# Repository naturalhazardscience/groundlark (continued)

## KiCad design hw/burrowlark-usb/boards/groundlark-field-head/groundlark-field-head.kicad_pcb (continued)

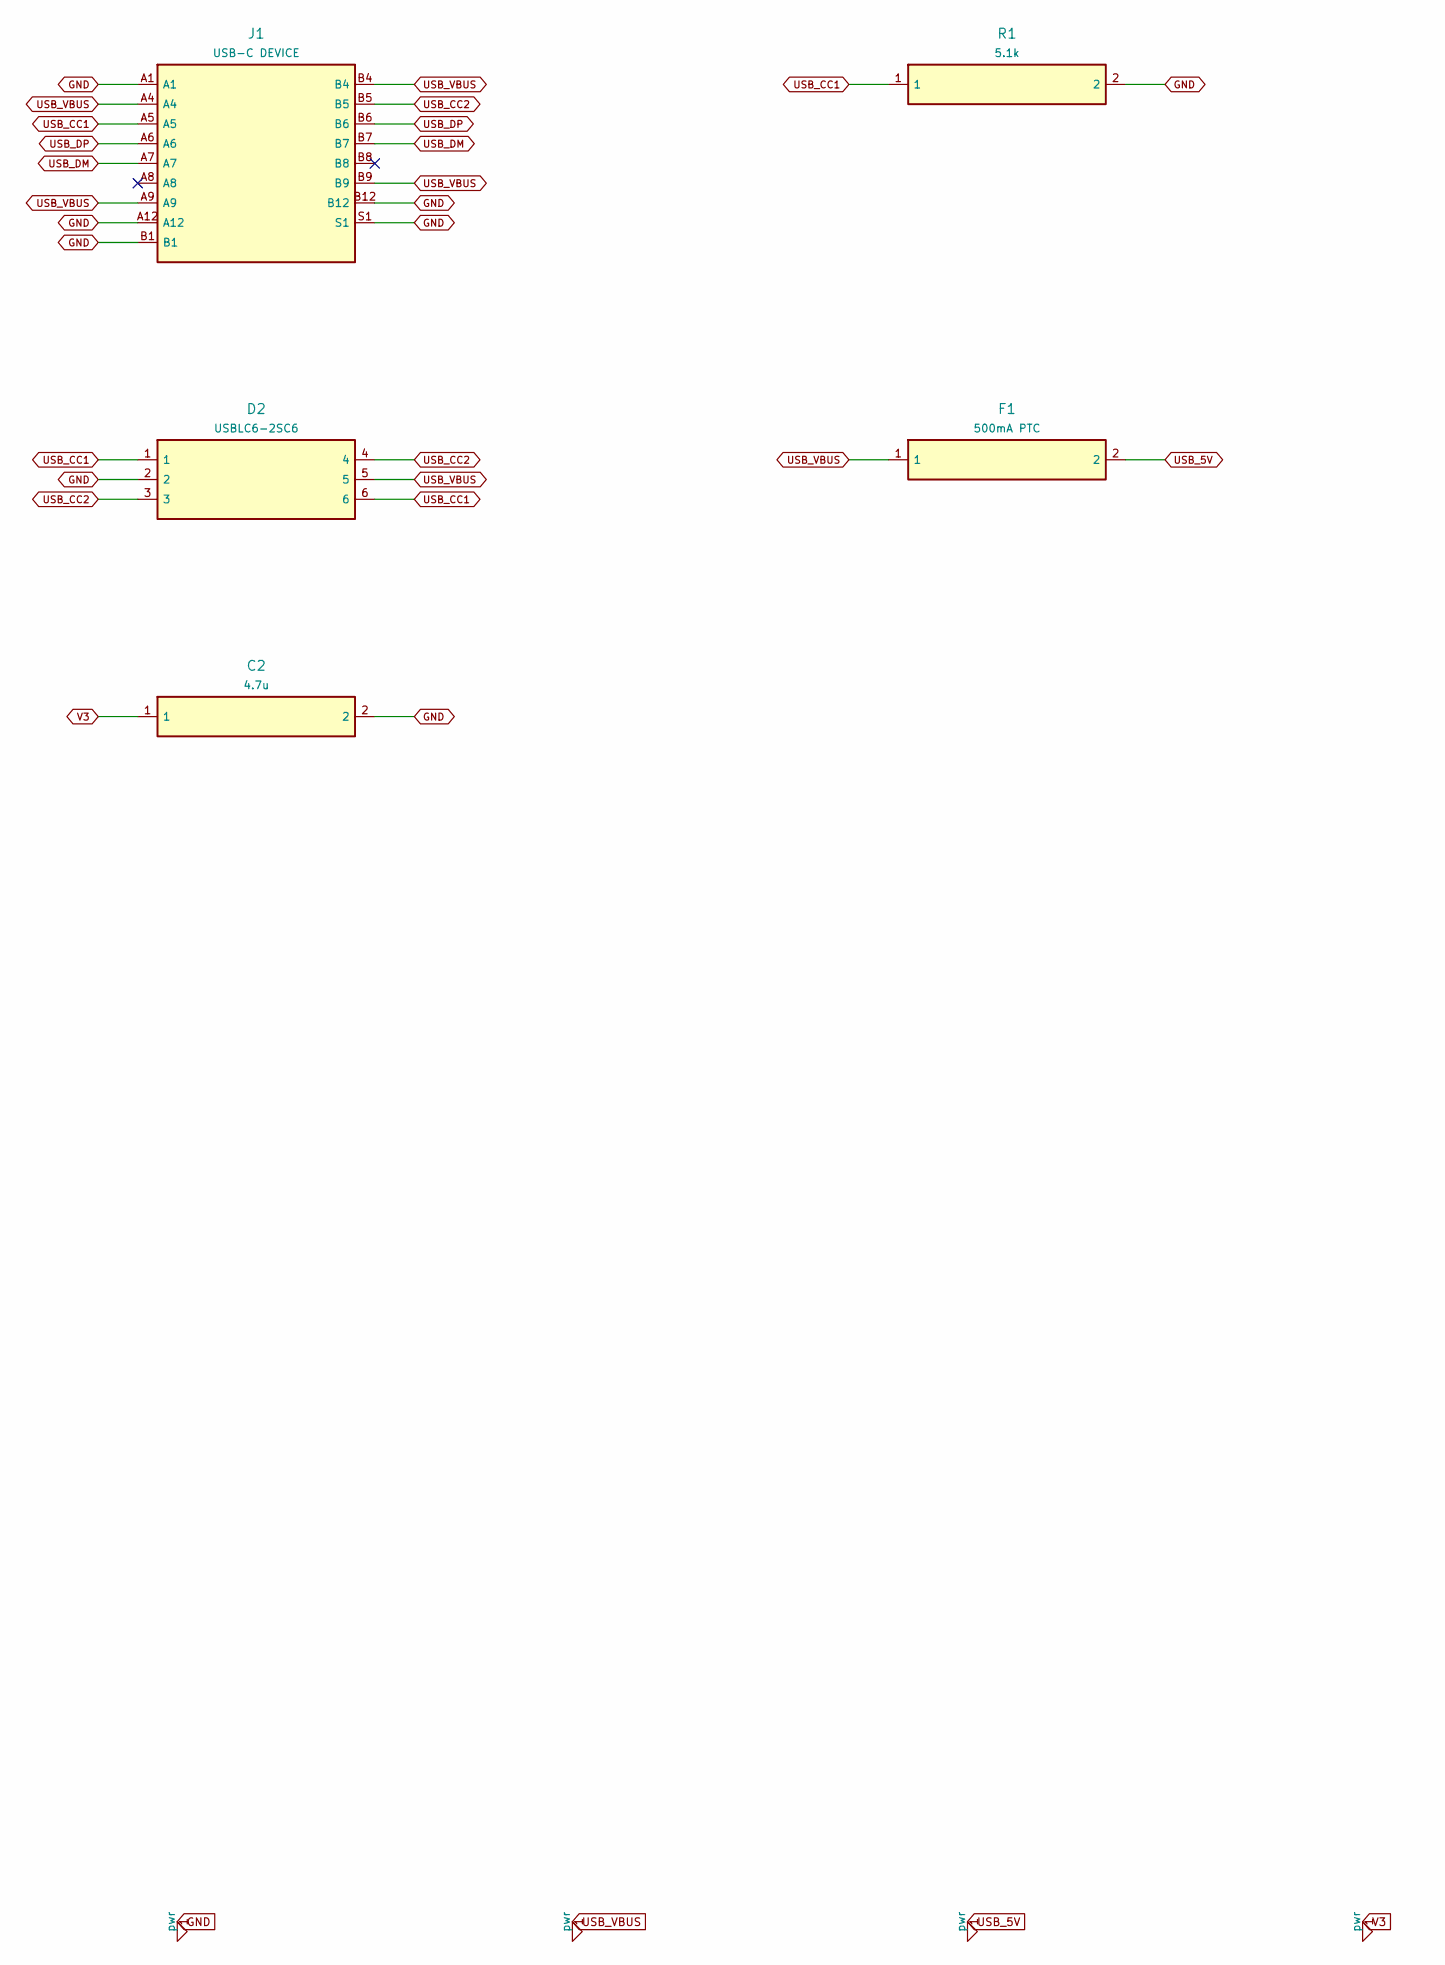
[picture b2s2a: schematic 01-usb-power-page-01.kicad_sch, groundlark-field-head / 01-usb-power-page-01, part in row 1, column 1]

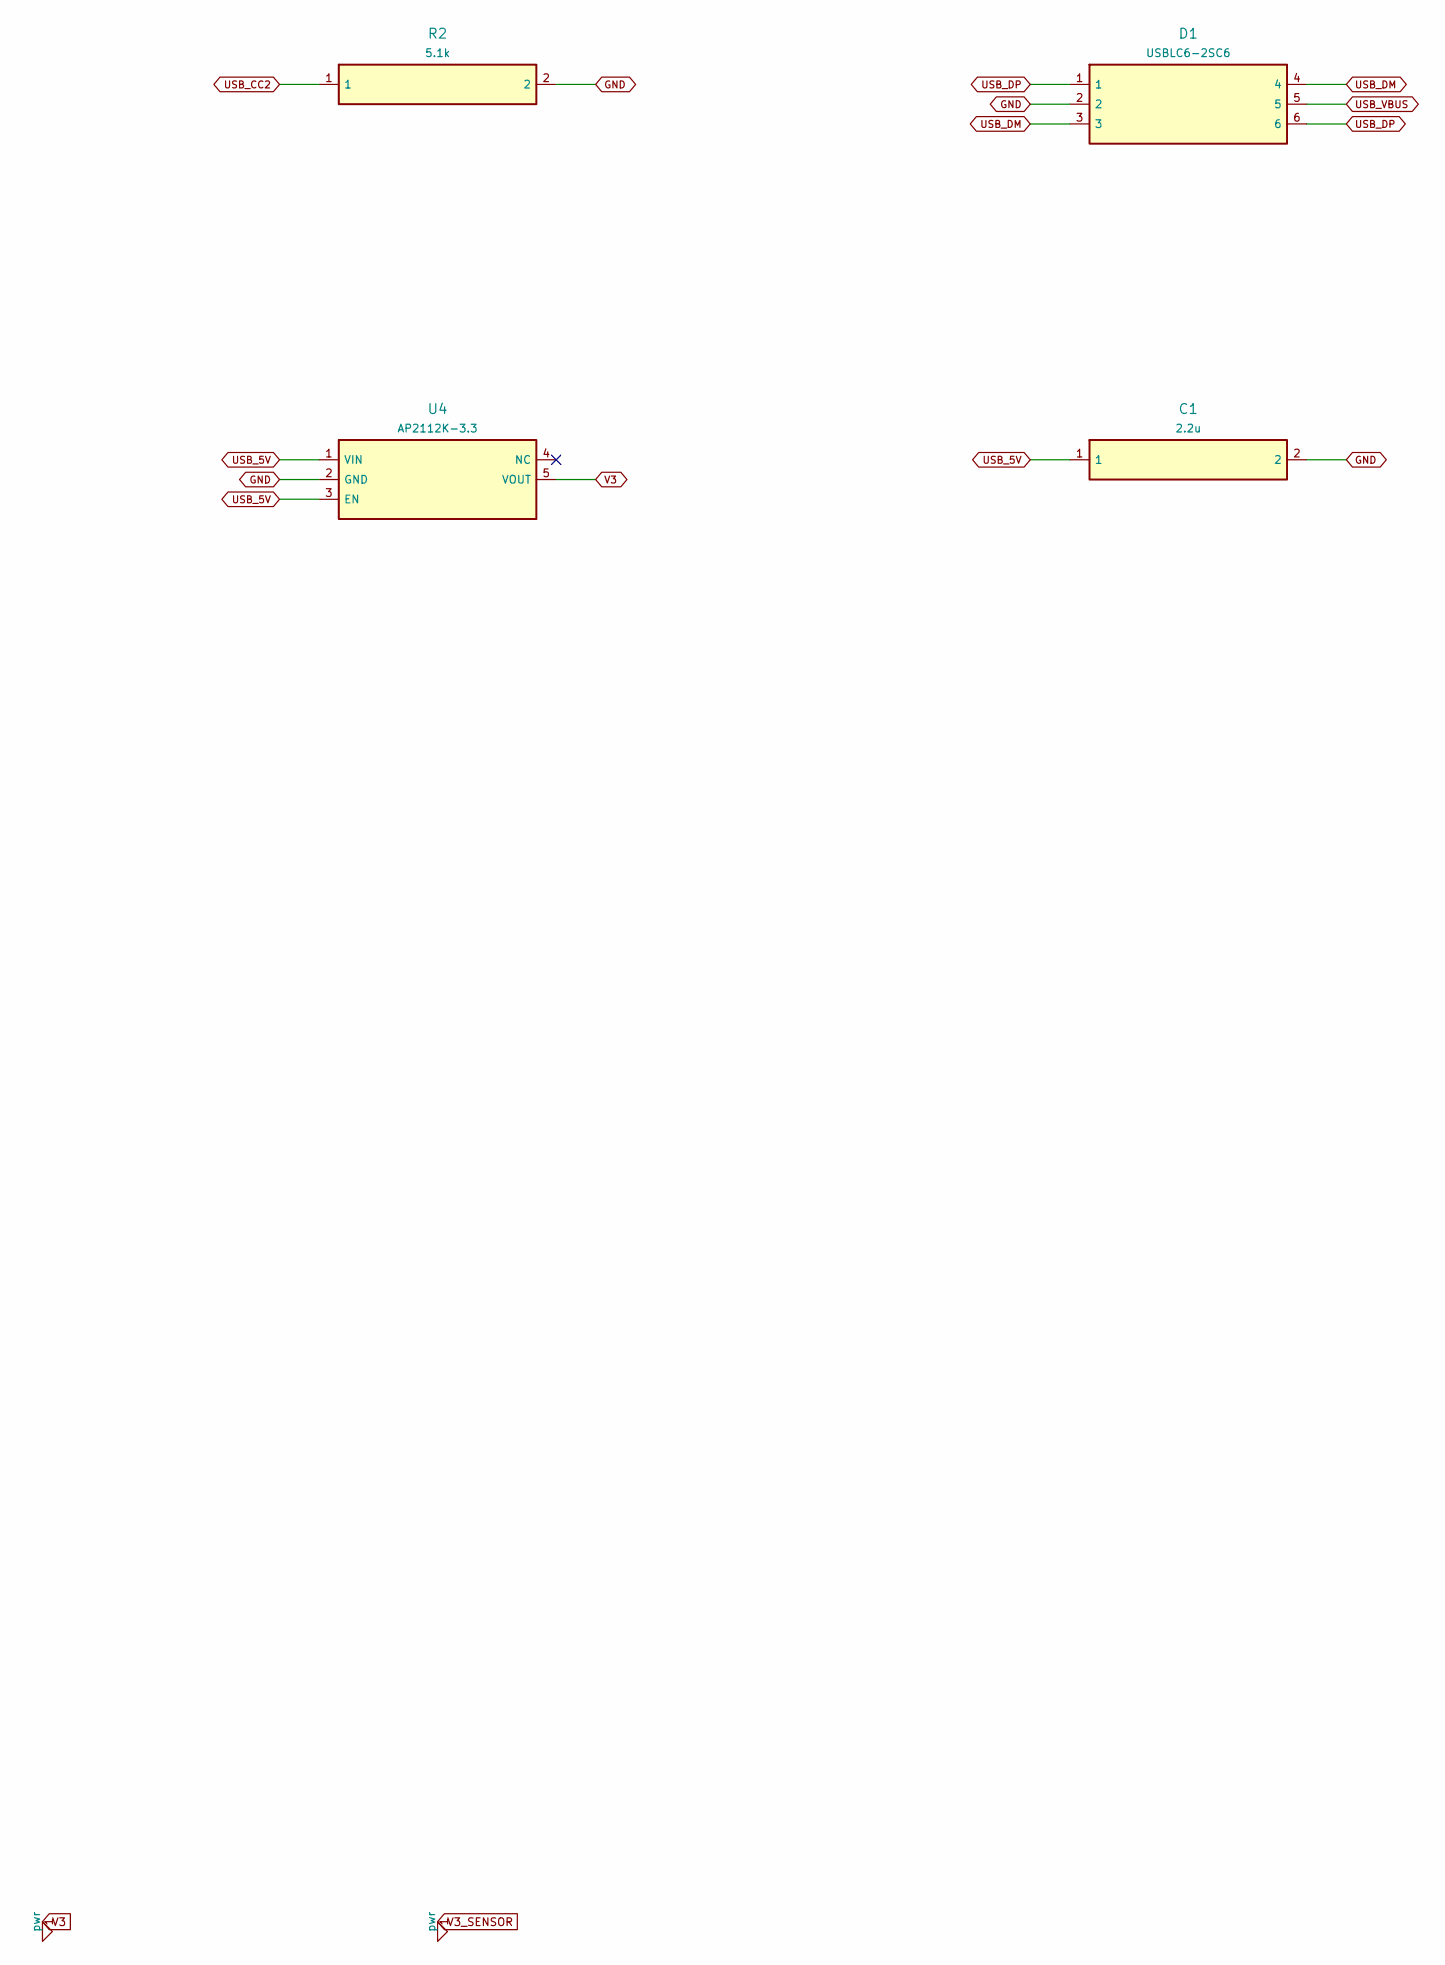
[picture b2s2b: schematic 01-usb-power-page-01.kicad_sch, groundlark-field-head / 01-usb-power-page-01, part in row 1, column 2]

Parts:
C1: 2.2u; Capacitor_SMD__C_0805_2012Metric; MPN GRM21BR71E225KA73L
C2: 4.7u; Capacitor_SMD__C_0805_2012Metric; MPN GRM21BR71A475KA73L
D1, D2: USBLC6-2SC6; Package_TO_SOT_SMD__SOT-23-6; MPN USBLC6-2SC6
F1: 500mA PTC; Fuse__Fuse_1812_4532Metric; MPN MF-MSMF050-2
J1: USB-C DEVICE; Connector_USB__USB_C_Receptacle_GCT_USB4105-xx-A_16P_TopMnt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; MPN USB4105-GF-A
R1, R2: 5.1k; Resistor_SMD__R_0603_1608Metric; MPN RC0603FR-075K1L
U4: AP2112K-3.3; Package_TO_SOT_SMD__SOT-23-5; MPN AP2112K-3.3TRG1

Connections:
4: U4.4 (NC)
A8: J1.A8
B8: J1.B8
GND: C1.2, C2.2, D1.2, D2.2, J1.A1, J1.A12, J1.B1, J1.B12, J1.S1, R1.2, R2.2, U4.2 (GND); also elsewhere on the board
USB_5V: C1.1, F1.2, U4.1 (VIN), U4.3 (EN)
USB_CC1: D2.1, D2.6, J1.A5, R1.1
USB_CC2: D2.3, D2.4, J1.B5, R2.1
USB_DM: D1.3, D1.4, J1.A7, J1.B7; also elsewhere on the board
USB_DP: D1.1, D1.6, J1.A6, J1.B6; also elsewhere on the board
USB_VBUS: D1.5, D2.5, F1.1, J1.A4, J1.A9, J1.B4, J1.B9
V3: C2.1, U4.5 (VOUT); also elsewhere on the board

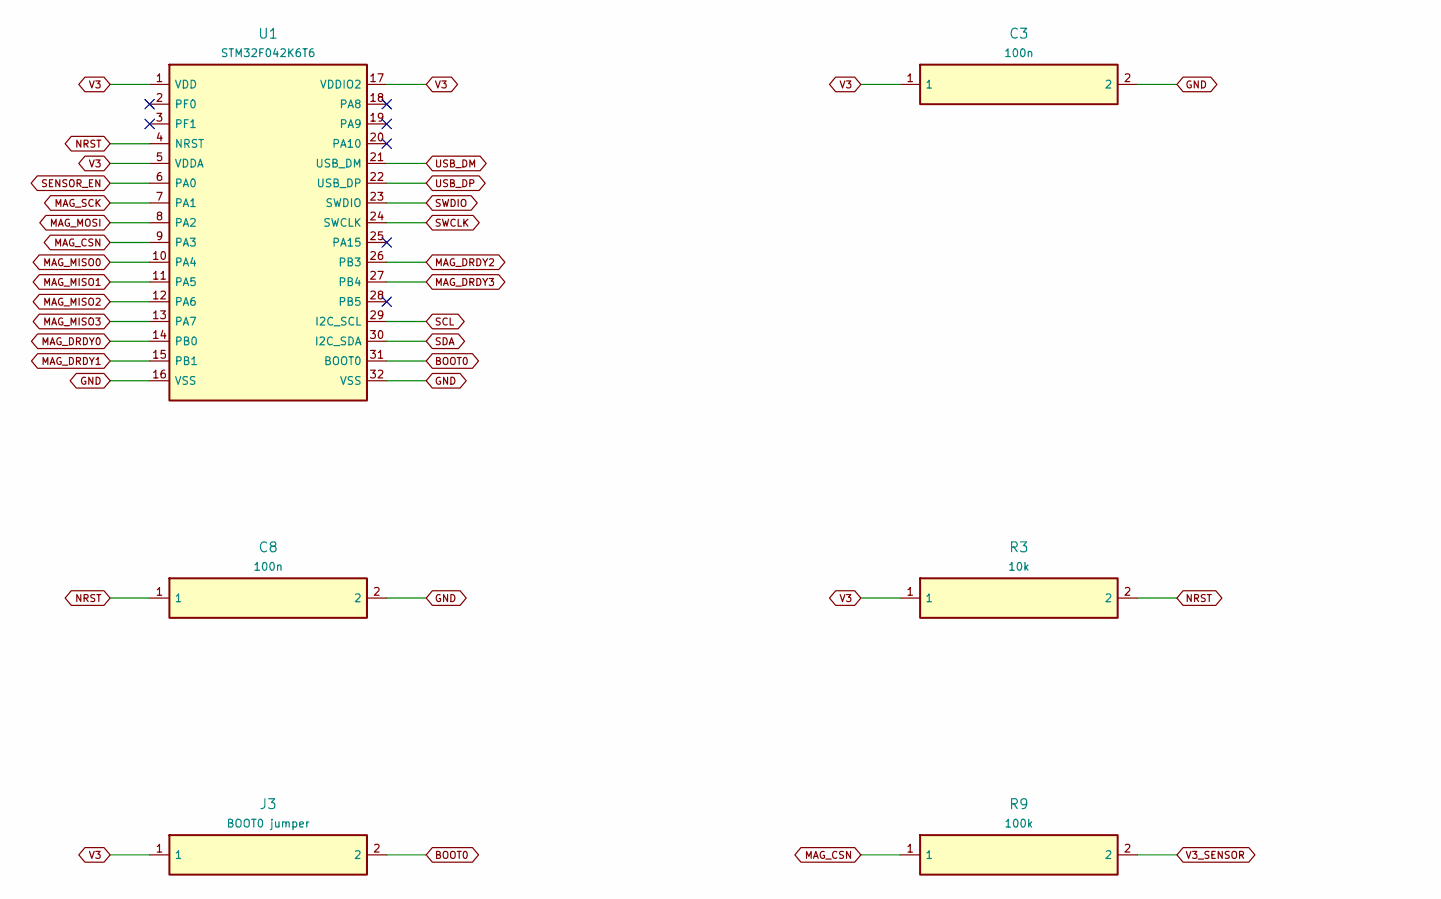
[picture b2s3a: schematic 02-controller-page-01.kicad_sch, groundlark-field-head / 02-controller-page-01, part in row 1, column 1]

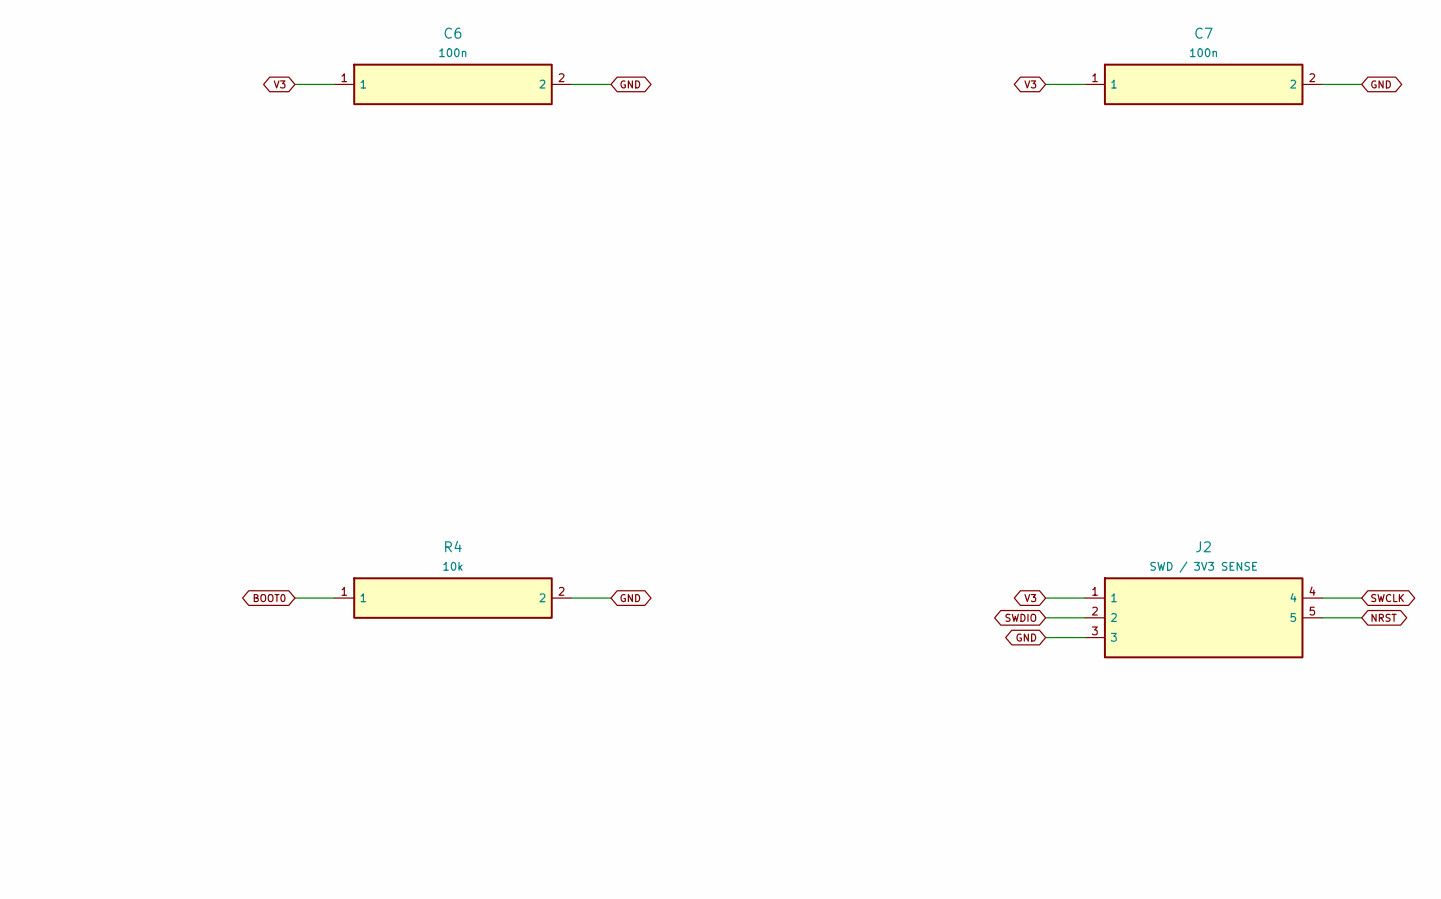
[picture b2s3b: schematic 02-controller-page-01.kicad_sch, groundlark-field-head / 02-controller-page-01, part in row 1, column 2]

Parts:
C3, C6, C7, C8: 100n; Capacitor_SMD__C_0603_1608Metric; MPN GRM188R71H104KA93D
J2: SWD / 3V3 SENSE; Connector_PinHeader_2.54mm__PinHeader_1x05_P2.54mm_Vertical; MPN M20-9990545
J3: BOOT0 jumper; Connector_PinHeader_2.54mm__PinHeader_1x02_P2.54mm_Vertical; MPN EEPROM write enable
R3, R4: 10k; Resistor_SMD__R_0603_1608Metric; MPN RC0603FR-0710KL
R9: 100k; Resistor_SMD__R_0603_1608Metric; MPN RC0603FR-07100KL
U1: STM32F042K6T6; Package_QFP__LQFP-32_7x7mm_P0.8mm; MPN STM32F042K6T6

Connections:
2: U1.2 (PF0)
3: U1.3 (PF1)
18: U1.18 (PA8)
19: U1.19 (PA9)
20: U1.20 (PA10)
25: U1.25 (PA15)
28: U1.28 (PB5)
BOOT0: J3.2, R4.1, U1.31 (BOOT0)
GND: C3.2, C6.2, C7.2, C8.2, J2.3, R4.2, U1.16 (VSS), U1.32 (VSS); also elsewhere on the board
MAG_CSN: R9.1, U1.9 (PA3); also elsewhere on the board
MAG_DRDY0: U1.14 (PB0); also elsewhere on the board
MAG_DRDY1: U1.15 (PB1); also elsewhere on the board
MAG_DRDY2: U1.26 (PB3); also elsewhere on the board
MAG_DRDY3: U1.27 (PB4); also elsewhere on the board
MAG_MISO0: U1.10 (PA4); also elsewhere on the board
MAG_MISO1: U1.11 (PA5); also elsewhere on the board
MAG_MISO2: U1.12 (PA6); also elsewhere on the board
MAG_MISO3: U1.13 (PA7); also elsewhere on the board
MAG_MOSI: U1.8 (PA2); also elsewhere on the board
MAG_SCK: U1.7 (PA1); also elsewhere on the board
NRST: C8.1, J2.5, R3.2, U1.4 (NRST)
SCL: U1.29 (I2C_SCL); also elsewhere on the board
SDA: U1.30 (I2C_SDA); also elsewhere on the board
SENSOR_EN: U1.6 (PA0); also elsewhere on the board
SWCLK: J2.4, U1.24 (SWCLK)
SWDIO: J2.2, U1.23 (SWDIO)
USB_DM: U1.21 (USB_DM); also elsewhere on the board
USB_DP: U1.22 (USB_DP); also elsewhere on the board
V3: C3.1, C6.1, C7.1, J2.1, J3.1, R3.1, U1.1 (VDD), U1.5 (VDDA), U1.17 (VDDIO2); also elsewhere on the board
V3_SENSOR: R9.2; also elsewhere on the board

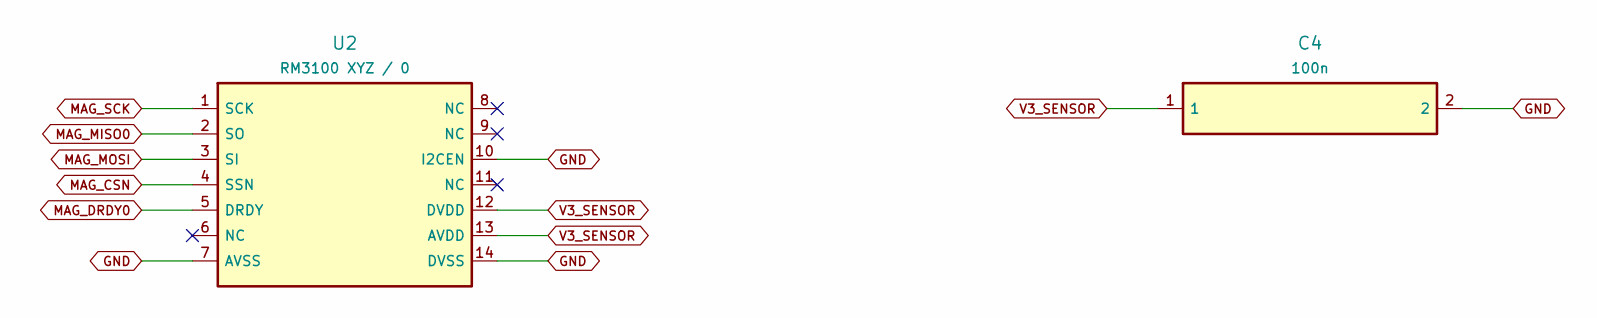
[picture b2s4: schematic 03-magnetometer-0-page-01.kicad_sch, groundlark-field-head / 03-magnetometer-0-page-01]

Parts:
C4: 100n; Capacitor_SMD__C_0603_1608Metric; MPN GRM188R71H104KA93D
U2: RM3100 XYZ / 0; Groundlark__PNI_14190_Module; MPN PNI 14190

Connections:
6: U2.6 (NC)
8: U2.8 (NC)
9: U2.9 (NC)
11: U2.11 (NC)
GND: C4.2, U2.7 (AVSS), U2.10 (I2CEN), U2.14 (DVSS); also elsewhere on the board
MAG_CSN: U2.4 (SSN); also elsewhere on the board
MAG_DRDY0: U2.5 (DRDY); also elsewhere on the board
MAG_MISO0: U2.2 (SO); also elsewhere on the board
MAG_MOSI: U2.3 (SI); also elsewhere on the board
MAG_SCK: U2.1 (SCK); also elsewhere on the board
V3_SENSOR: C4.1, U2.12 (DVDD), U2.13 (AVDD); also elsewhere on the board

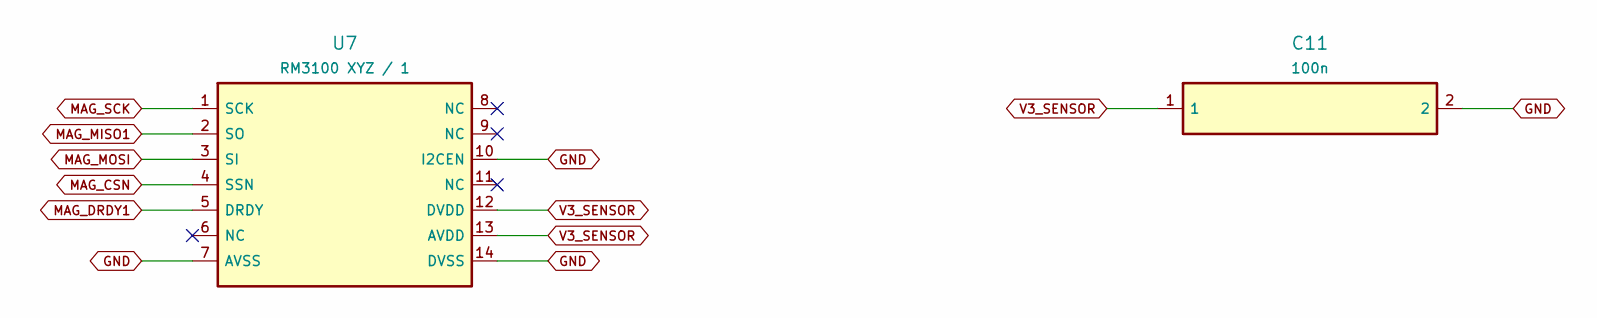
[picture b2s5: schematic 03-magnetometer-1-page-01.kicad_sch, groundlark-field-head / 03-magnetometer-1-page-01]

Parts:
C11: 100n; Capacitor_SMD__C_0603_1608Metric; MPN GRM188R71H104KA93D
U7: RM3100 XYZ / 1; Groundlark__PNI_14190_Module; MPN PNI 14190

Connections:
GND: C11.2, U7.7 (AVSS), U7.10 (I2CEN), U7.14 (DVSS); also elsewhere on the board
MAG_CSN: U7.4 (SSN); also elsewhere on the board
MAG_DRDY1: U7.5 (DRDY); also elsewhere on the board
MAG_MISO1: U7.2 (SO); also elsewhere on the board
MAG_MOSI: U7.3 (SI); also elsewhere on the board
MAG_SCK: U7.1 (SCK); also elsewhere on the board
V3_SENSOR: C11.1, U7.12 (DVDD), U7.13 (AVDD); also elsewhere on the board
u7-6: U7.6 (NC)
u7-8: U7.8 (NC)
u7-9: U7.9 (NC)
u7-11: U7.11 (NC)

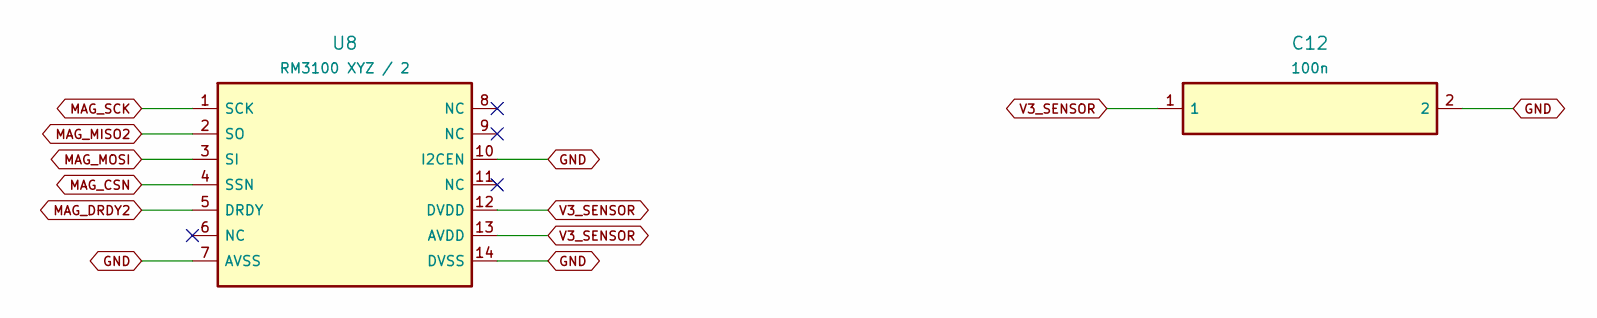
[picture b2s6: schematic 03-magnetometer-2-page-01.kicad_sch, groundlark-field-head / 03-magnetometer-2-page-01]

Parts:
C12: 100n; Capacitor_SMD__C_0603_1608Metric; MPN GRM188R71H104KA93D
U8: RM3100 XYZ / 2; Groundlark__PNI_14190_Module; MPN PNI 14190

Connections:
GND: C12.2, U8.7 (AVSS), U8.10 (I2CEN), U8.14 (DVSS); also elsewhere on the board
MAG_CSN: U8.4 (SSN); also elsewhere on the board
MAG_DRDY2: U8.5 (DRDY); also elsewhere on the board
MAG_MISO2: U8.2 (SO); also elsewhere on the board
MAG_MOSI: U8.3 (SI); also elsewhere on the board
MAG_SCK: U8.1 (SCK); also elsewhere on the board
V3_SENSOR: C12.1, U8.12 (DVDD), U8.13 (AVDD); also elsewhere on the board
u8-6: U8.6 (NC)
u8-8: U8.8 (NC)
u8-9: U8.9 (NC)
u8-11: U8.11 (NC)

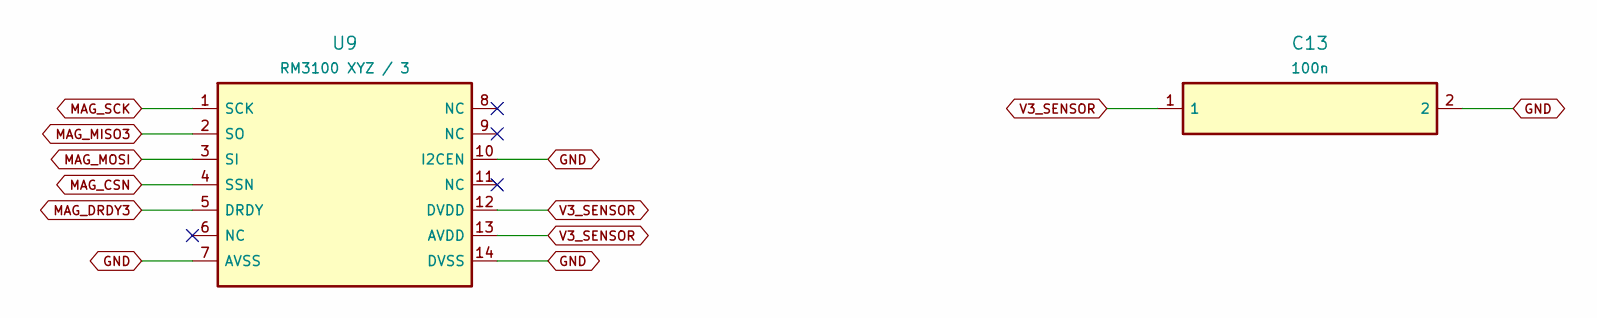
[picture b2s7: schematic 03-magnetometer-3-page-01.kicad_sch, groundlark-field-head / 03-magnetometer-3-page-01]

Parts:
C13: 100n; Capacitor_SMD__C_0603_1608Metric; MPN GRM188R71H104KA93D
U9: RM3100 XYZ / 3; Groundlark__PNI_14190_Module; MPN PNI 14190

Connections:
GND: C13.2, U9.7 (AVSS), U9.10 (I2CEN), U9.14 (DVSS); also elsewhere on the board
MAG_CSN: U9.4 (SSN); also elsewhere on the board
MAG_DRDY3: U9.5 (DRDY); also elsewhere on the board
MAG_MISO3: U9.2 (SO); also elsewhere on the board
MAG_MOSI: U9.3 (SI); also elsewhere on the board
MAG_SCK: U9.1 (SCK); also elsewhere on the board
V3_SENSOR: C13.1, U9.12 (DVDD), U9.13 (AVDD); also elsewhere on the board
u9-6: U9.6 (NC)
u9-8: U9.8 (NC)
u9-9: U9.9 (NC)
u9-11: U9.11 (NC)

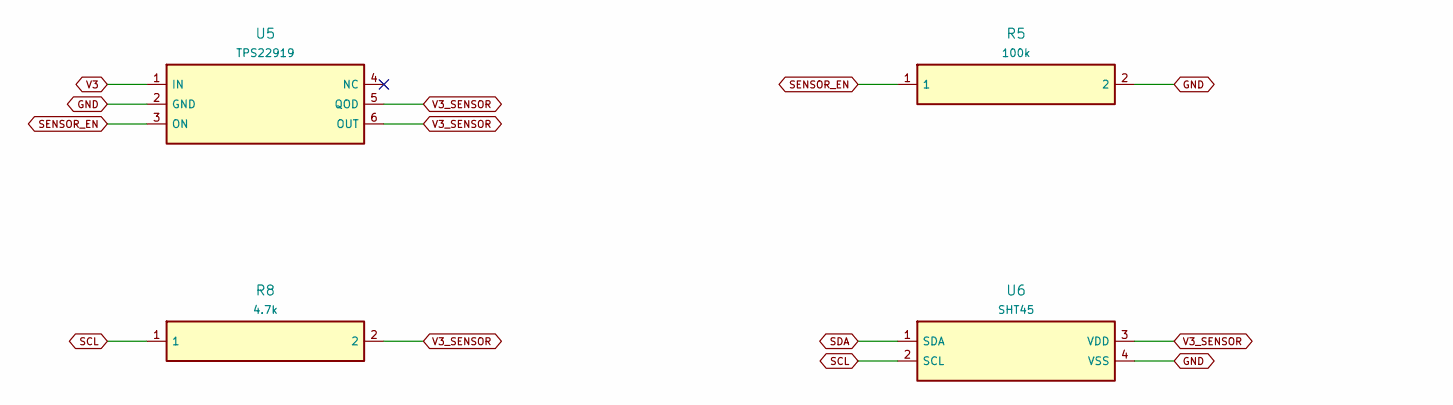
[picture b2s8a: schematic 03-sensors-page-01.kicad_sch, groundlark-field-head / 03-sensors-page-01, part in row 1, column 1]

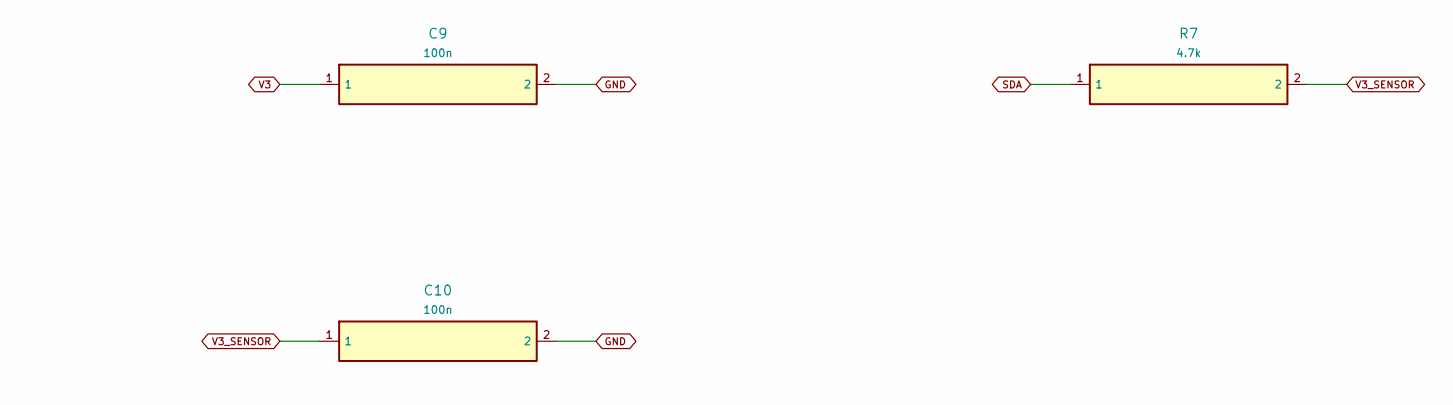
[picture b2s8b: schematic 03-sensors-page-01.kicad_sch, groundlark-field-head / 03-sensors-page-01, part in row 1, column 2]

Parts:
C9, C10: 100n; Capacitor_SMD__C_0603_1608Metric; MPN GRM188R71H104KA93D
R5: 100k; Resistor_SMD__R_0603_1608Metric; MPN RC0603FR-07100KL
R7, R8: 4.7k; Resistor_SMD__R_0603_1608Metric; MPN RC0603FR-074K7L
U5: TPS22919; Package_TO_SOT_SMD__SOT-363_SC-70-6; MPN TPS22919DCKR
U6: SHT45; MPN SHT45-AD1B-R2

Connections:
GND: C9.2, C10.2, R5.2, U5.2 (GND), U6.4 (VSS); also elsewhere on the board
SCL: R8.1, U6.2 (SCL); also elsewhere on the board
SDA: R7.1, U6.1 (SDA); also elsewhere on the board
SENSOR_EN: R5.1, U5.3 (ON); also elsewhere on the board
V3: C9.1, U5.1 (IN); also elsewhere on the board
V3_SENSOR: C10.1, R7.2, R8.2, U5.5 (QOD), U5.6 (OUT), U6.3 (VDD); also elsewhere on the board
u5-4: U5.4 (NC)

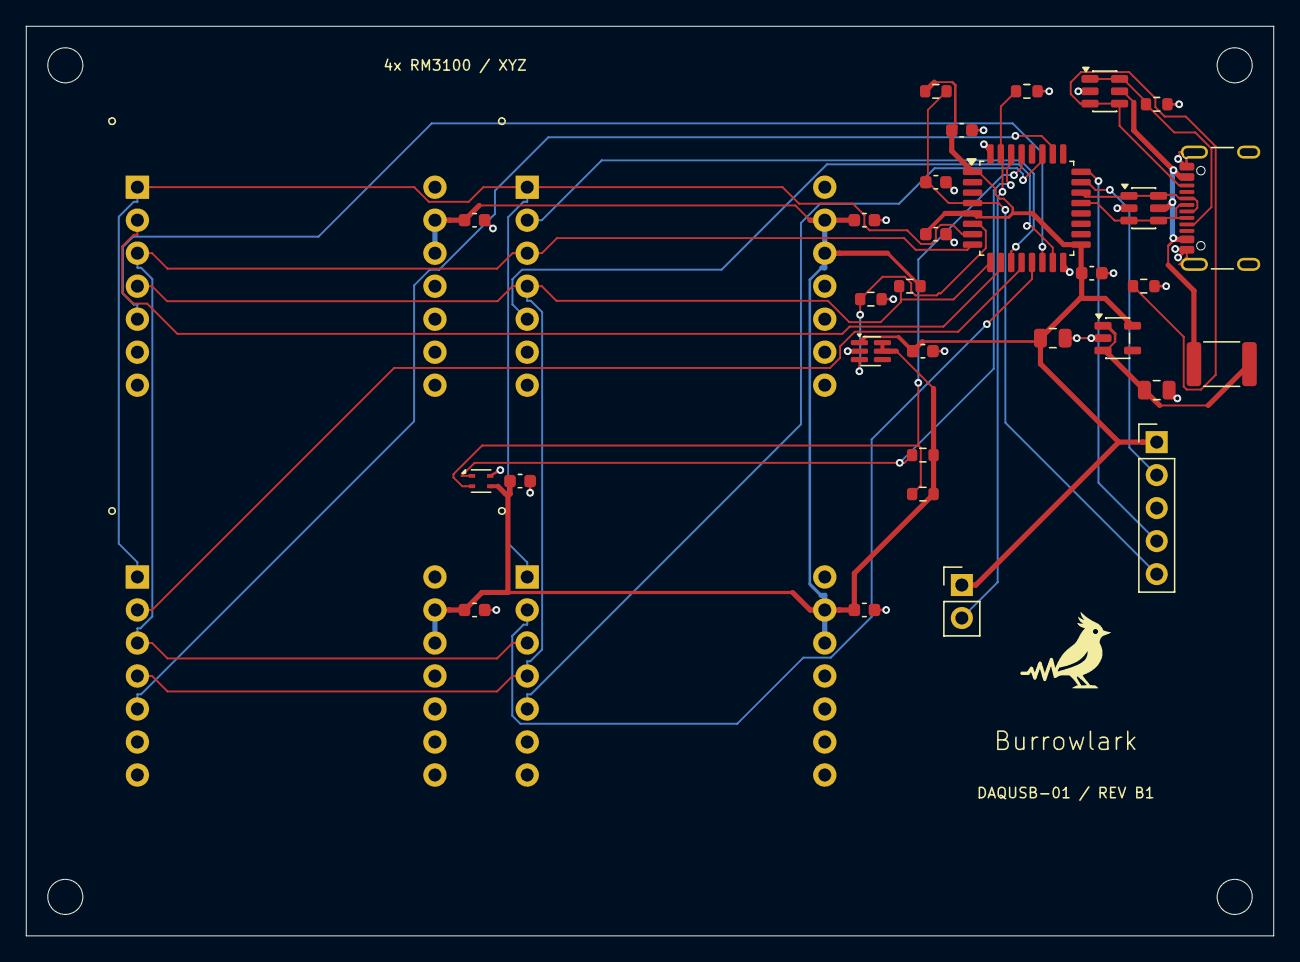
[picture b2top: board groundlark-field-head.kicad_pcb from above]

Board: 4 copper layers, 96.0 x 70.0 mm, 38 parts (0 on the bottom side), 27 nets.

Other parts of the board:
H1, H2, H3, H4: M2.5 NPTH; MountingHole__MountingHole_2.7mm_M2.5

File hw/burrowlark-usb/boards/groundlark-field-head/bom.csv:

Reference,Value,MPN,Footprint,DNP,Note
J1,USB-C DEVICE,USB4105-GF-A,Connector_USB__USB_C_Receptacle_GCT_USB4105-xx-A_16P_TopMnt_Horizontal,False,
R1,5.1k,RC0603FR-075K1L,Resistor_SMD__R_0603_1608Metric,False,
R2,5.1k,RC0603FR-075K1L,Resistor_SMD__R_0603_1608Metric,False,
D1,USBLC6-2SC6,USBLC6-2SC6,Package_TO_SOT_SMD__SOT-23-6,False,
D2,USBLC6-2SC6,USBLC6-2SC6,Package_TO_SOT_SMD__SOT-23-6,False,
F1,500mA PTC,MF-MSMF050-2,Fuse__Fuse_1812_4532Metric,False,
U4,AP2112K-3.3,AP2112K-3.3TRG1,Package_TO_SOT_SMD__SOT-23-5,False,
C1,2.2u,GRM21BR71E225KA73L,Capacitor_SMD__C_0805_2012Metric,False,
C2,4.7u,GRM21BR71A475KA73L,Capacitor_SMD__C_0805_2012Metric,False,
U1,STM32F042K6T6,STM32F042K6T6,Package_QFP__LQFP-32_7x7mm_P0.8mm,False,
C3,100n,GRM188R71H104KA93D,Capacitor_SMD__C_0603_1608Metric,False,
C6,100n,GRM188R71H104KA93D,Capacitor_SMD__C_0603_1608Metric,False,
C7,100n,GRM188R71H104KA93D,Capacitor_SMD__C_0603_1608Metric,False,
C8,100n,GRM188R71H104KA93D,Capacitor_SMD__C_0603_1608Metric,False,
R3,10k,RC0603FR-0710KL,Resistor_SMD__R_0603_1608Metric,False,
R4,10k,RC0603FR-0710KL,Resistor_SMD__R_0603_1608Metric,False,
J2,SWD / 3V3 SENSE,M20-9990545,Connector_PinHeader_2.54mm__PinHeader_1x05_P2.54mm_Vertical,False,Pin 1 is target voltage sense; do not externally power the rail
J3,BOOT0 jumper,EEPROM write enable,Connector_PinHeader_2.54mm__PinHeader_1x02_P2.54mm_Vertical,False,
U5,TPS22919,TPS22919DCKR,Package_TO_SOT_SMD__SOT-363_SC-70-6,False,
R5,100k,RC0603FR-07100KL,Resistor_SMD__R_0603_1608Metric,False,
C9,100n,GRM188R71H104KA93D,Capacitor_SMD__C_0603_1608Metric,False,
R7,4.7k,RC0603FR-074K7L,Resistor_SMD__R_0603_1608Metric,False,
R8,4.7k,RC0603FR-074K7L,Resistor_SMD__R_0603_1608Metric,False,
U2,RM3100 XYZ / 0,PNI 14190,Groundlark__PNI_14190_Module,False,Array slot 0; parallel SPI; module top-view orientation identical for all four; NC 6/8/9/11
C4,100n,GRM188R71H104KA93D,Capacitor_SMD__C_0603_1608Metric,False,U2 local 100 nF bypass
H1,M2.5 NPTH,M2.5 NPTH,MountingHole__MountingHole_2.7mm_M2.5,False,
H2,M2.5 NPTH,M2.5 NPTH,MountingHole__MountingHole_2.7mm_M2.5,False,
H3,M2.5 NPTH,M2.5 NPTH,MountingHole__MountingHole_2.7mm_M2.5,False,
H4,M2.5 NPTH,M2.5 NPTH,MountingHole__MountingHole_2.7mm_M2.5,False,
U6,SHT45,SHT45-AD1B-R2,SHT45,False,Enclosure temperature/humidity; 0x44; heater disabled; keep sensing opening exposed
C10,100n,GRM188R71H104KA93D,Capacitor_SMD__C_0603_1608Metric,False,SHT45 local bypass
U7,RM3100 XYZ / 1,PNI 14190,Groundlark__PNI_14190_Module,False,Array slot 1; parallel SPI; module top-view orientation identical for all four; NC 6/8/9/11
C11,100n,GRM188R71H104KA93D,Capacitor_SMD__C_0603_1608Metric,False,U7 local 100 nF bypass
U8,RM3100 XYZ / 2,PNI 14190,Groundlark__PNI_14190_Module,False,Array slot 2; parallel SPI; module top-view orientation identical for all four; NC 6/8/9/11
C12,100n,GRM188R71H104KA93D,Capacitor_SMD__C_0603_1608Metric,False,U8 local 100 nF bypass
U9,RM3100 XYZ / 3,PNI 14190,Groundlark__PNI_14190_Module,False,Array slot 3; parallel SPI; module top-view orientation identical for all four; NC 6/8/9/11
C13,100n,GRM188R71H104KA93D,Capacitor_SMD__C_0603_1608Metric,False,U9 local 100 nF bypass
R9,100k,RC0603FR-07100KL,Resistor_SMD__R_0603_1608Metric,False,100 kohm shared SPI CS pull-up to switched sensor rail
